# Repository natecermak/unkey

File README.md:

# Acoustic Underwater Text-based Communication Device (Name TBD)

## Purpose/Motivation
Divers often need to communicate with one another or with a dive boat, but typically can only communicate when in visual range of each other. A simple means to communicate with a bandwidth of text messaging (~40 wpm) over distances of several hundred meters could potentially save lives when if other divers or the dive boat can be made aware of and respond to unexpected conditions/situations.

## Communication scheme overview
Acoustic communication is basically the only feasible scheme underwater, and hence has been the standard for underwater communication since at least the early 1900s. Electromagnetic signals penetrate very poorly underwater, so convential means of communication (cellular communication, radio/walkie-talkies, bluetooth, wifi) are not feasible. Optical signaling is sometimes feasible (e.g. with flashlights), but relies on line of sight and good water clarity, and has limited range due to scattering and absorption underwater. However, if one has ever heard dolphins or whales underwater, they can attest to the immense distances these signals can travel, greatly exceeding the distance one can see underwater.

Underwater environments (a) add a lot of noise and (b) distort signals due to reflections.

Here, we use **binary frequency-shift keying (BFSK)** to send bits. See [Transmit / Receive Signal Flow](#transmit--receive-signal-flow) for how modulation and demodulation work.

## Subsystems:

### Keyboard
To get around difficulties with mechanical keys, we chose to use magnetic sensors and a magnet-bearing stylus. Underwater, mechanical keys have several failure modes:
 - They can break in such a way that allows water into the device, and
 - As one goes underwater, pressure increases, which eventually can press keys on its own, at which point buttons are stuck in the 'pressed' state, and basically useless.
We chose to use omnipolar Hall-effect switches, which have a digital output that changes from high to low when the magnetic flux through the device increases beyond some threshold. We rapidly read out every key's on/off state using an array of daisy-chained shift registers, an approach commonly used in other keyboards. When the user brings the magnet-tipped stylus near a sensor "key", the microcontroller can read the change in the Hall-effect switch output.

Users typically prefer some tactile feedback when they hit a key, and this system doesn't naturally provide that. As such, we experimented with adding a soft (low coercivity) magnetic material (1-2mm mild steel ball bearings) above the Hall-effect sensor, to provide a small pull-in magnetic force when the stylus is brought close to the key. This provides tacticle sensation to the user that they have actually touched a key. It's essential that this material is magnetizable so that it attracts the stylus, but also that it cannot develop a permanent magnetic moment. If it were to develop a permanent magnetic moment, it would turn the Hall-effect sensor on all the time and the key would be stuck "on".

Keyboard layout:
---------- Default, no modifier -------
1   2   3   4   5   6   7   8   9   0
q   w   e   r   t   y   u   i   o   p
  a   s   d   f   g   h   j   k   l   DEL
CAP z   x   c   v   b   n   m   ?   BCK
SYM      SPACESPACESPACESP   ,   .    RET
(plus 6 arrow keys, SEND)

---------- SYM modifier ---------------
!   @   #   $   %   ^   &   *   (   )
`   ~   -   _   =   +   :   ;   '   "
  [   ]   {   }   |   \   /   <   >   DEL
CAP z   x   c   v   b   n   m   ?   BCK
SYM      SPACESPACESPACESP   ,   .    RET

key count is:
    row 1: 10 keys
    row 2: 10 keys
    row 3: 10 keys
    row 4: 10 keys
    row 5: 5 keys
    off-grid: 6 arrow keys, 1 SEND key
Total: 52 keys

Non-character keys: 6 arrow keys, SEND, BCK, DEL, CAP, SYM

Future work could use open-drain hall-effect sensors in a grid to give more precise hit-boxes (e.g. a 2x2 grid of AH1925-HK4-7, wired in parallel, for each key). However, this would be significantly more expensive, as it would require roughly 4x as many switches.

### Microcontroller
We use a Teensy 4.1 microcontroller due to ease of development. Essential features this microcontroller provides are:
 - rapid (~100 ksps) ADC readout via DMA
 - SPI peripheral for driving a TFT LCD scree
n - DMA-compatible SPI peripheral for driving a DAC
 - I2C peripheral for controlling an external switch matrix
However, many other microcontrollers would likely work fine for this system.

### Battery
We use a rechargeable lithium ion battery, which provides a nominal 3.7V input.

### Transducer
We use a 45mm x 45mm x 1.4mm square piezo plate from Steminc (SMPL45W45T14111) as a transducer. This piezo is spec'd as having a capacitance of 5.4nF +- 20%. It's made from material SM111, which has a piezo d33 constant of 320e-12 C/N.

We made some measurements of the impedance at various frequencies:
    - Frequency   Real      Imaginary     (Capacitance, Q)
    -  0.1 kHz:   570    -  103.5k imag   (15.3nF, Q=182)
    -  1.0 kHz:    45    -   10.42k imag  (15.3nF, Q=236)
    - 10.0 kHz:     2.9  -    1.03k imag  (15.4nF, Q=356)
    - 40.0 kHz:     2.25 -       63 imag  (63.0nF, Q=28)
    -100.0 kHz:    -0.09 -      132 imag  (12nF,   Q=1350)

Overall, this seems pretty discrepant with their claim of 5.4nF. Given two parallel plates of this size, separated by 1.4mm, and a dielectric constant of 1400 (also from the [SM111 materials page](http://www.steminc.com/piezo/PZ_property.asp)), the calculated capacitance should be 17.9nF, closer to our measured value than their spec.

We also purchased several other transducers to try out, but have not yet used/characterized ther others:
- SMD25T14F15111 - Piezo Ceramic Disc 25x1.4mm R 1.5 Mhz          1.9 nF
- SMD50T21F1000R - Piezo Electric Disc 50x2.1mm R 1 MHz           10 nF

### Transducer driver

### Transducer sensor
We use a charge amplifier circuit with a configurable gain.

### Sensor data processing
We use Goertzel filters to extract amplitude and phase at a fixed set of frequencies.

### Screen
TBD.

### Enclosure
TBD.

## Version history:
v1.2 PCB changes:
 - [X] switch from teensy 4.1 to t4 for space
 - [X] add battery monitor circuitry
 - [X] replicate LiIon charger circuit on it https://github.com/adafruit/Adafruit-USB-LiIon-LiPoly-Charger-PCB/tree/master
 - [X] switch shift registers to qfn
 - [X] redo keyboard layout
 - [X] add 40-pin ZIF connector for 3.2" TFT from buydisplay.com
 - [X] make all passives 0402 for consistency
 - [X] add explicit space for screen
 - [X] add explicit space for battery
 - [X] add explicit space for Qi charger coil + PCB
 - [X] pull LAT down on MCP4, or just wire it out -- cant leave it floating
 - [X] CE on 5V boost wont work! needs to be always enabled, and drive a switch
 - [X] figure out FMARK and RD on ZIF connector for display: tested with them floating and display still works, so non-essential

v1.3 pcb
 - [X] split board into two separate parts with explicit design for overall assembly. This is for two reasons:
    1. so that I can do single-sided assembly on both pieces, but then have some parts sticking up (keyboard) and some facing down (teensy/driver electronics)
    2. it makes the face of the screen flush with the face of the magnetic switches.
 - [X] fix TFT connector pin numbering (it's backwards from the connector)
 - [X] make an attempt at a BOM

---
## Transmit / Receive Signal Flow

### Signal Modulation Process:

Unkey uses binary frequency-shift keying (BFSK) to transmit data acoustically. Each bit is encoded as a short sine wave at one of two fixed frequencies: one frequency represents a 0, and the other represents a 1. Bits are sent at a fixed bit rate, and bytes are transmitted MSB-first. Each packet begins with a known alternating preamble pattern, followed by framed payload bytes and an explicit footer. The preamble exists solely to help the receiver discover bit timing and alignment before attempting to decode data.

On the transmit side, text messages are packetized into bytes, converted into a bit stream, and then emitted as a sequence of tone windows via the DAC and piezo transducer. Each window contains a single tone corresponding to the current bit.

### Receiver Demodulation Process:

The receiver samples audio continuously using the ADC and DMA, processing fixed-size time windows of samples. For each window, it runs two Goertzel detectors—one tuned to each BFSK frequency—and measures their relative magnitudes. If neither tone is strong enough, the window is treated as noise and ignored.

Rather than assuming fixed timing, the receiver first builds a rolling history of recent window-level tone decisions. Once enough history is collected and the average signal strength is high enough, the receiver searches this history for the known alternating preamble pattern. It does this by trying both possible window alignments and checking for repeated tone flips; when a consistent pattern is found, bit boundaries are considered “locked.”

After timing is locked, each aligned window produces a real bit. These bits are accumulated and scanned for valid packet framing (header and footer). When a complete frame is detected, the payload is extracted, validated, and delivered to the chat system. If the signal weakens or framing fails for too long, the receiver drops alignment and returns to waiting for the preamble.

---

## Firmware File Organization

```
firmware/
├── platformio.ini
├── include/                  # All header files
│   ├── battery.h
│   ├── chat_logic.h
│   ├── comm.h
│   ├── config.h              # Shared constants, types, UI/chat/layout settings
│   ├── display.h
│   ├── goertzel.h
│   ├── hardware_config.h     # Pin assignments and hardware setup
│   └── keyboard.h
├── src/                      # Main firmware source code
│   ├── battery.cpp
│   ├── chat_logic.cpp        # Message buffer, scrolling, state management
│   ├── comm.cpp              # Encode/decode bits, tx/rx state
│   ├── display.cpp           # Drawing chat, keyboard, cursor
│   ├── goertzel.cpp          # Frequency detection (demodulation)
│   ├── keyboard.cpp          # Polling, key states, modifiers, stylus interaction
│   └── main.cpp              # Entry point: setup(), loop(), high-level orchestration
├── test/                     # Unit test suites (organized by feature and file)
│   ├── receiving/
│   │   ├── test_adc_buffer_full_interrupt/
│   │   │   └── adc_buffer_full_interrupt.cpp
│   │   ├── test_check_for_complete_packet/
│   │   │   └── check_for_complete_packet.cpp
│   │   ├── test_deliver_message/
│   │   │   └── deliver_message.cpp
│   │   ├── test_get_bit_from_top_frequency/
│   │   │   └── get_bit_from_top_frequency.cpp
│   │   ├── test_decode_single_bit_from_adc_window/
│   │   │   └── decode_single_bit_from_adc_window.cpp
│   ├── transmitting/
│   │   └── test_packetize_message/
│   │       └── packetize_message.cpp
│   ├── mock_display.cpp
│   └── mock_display.h
```

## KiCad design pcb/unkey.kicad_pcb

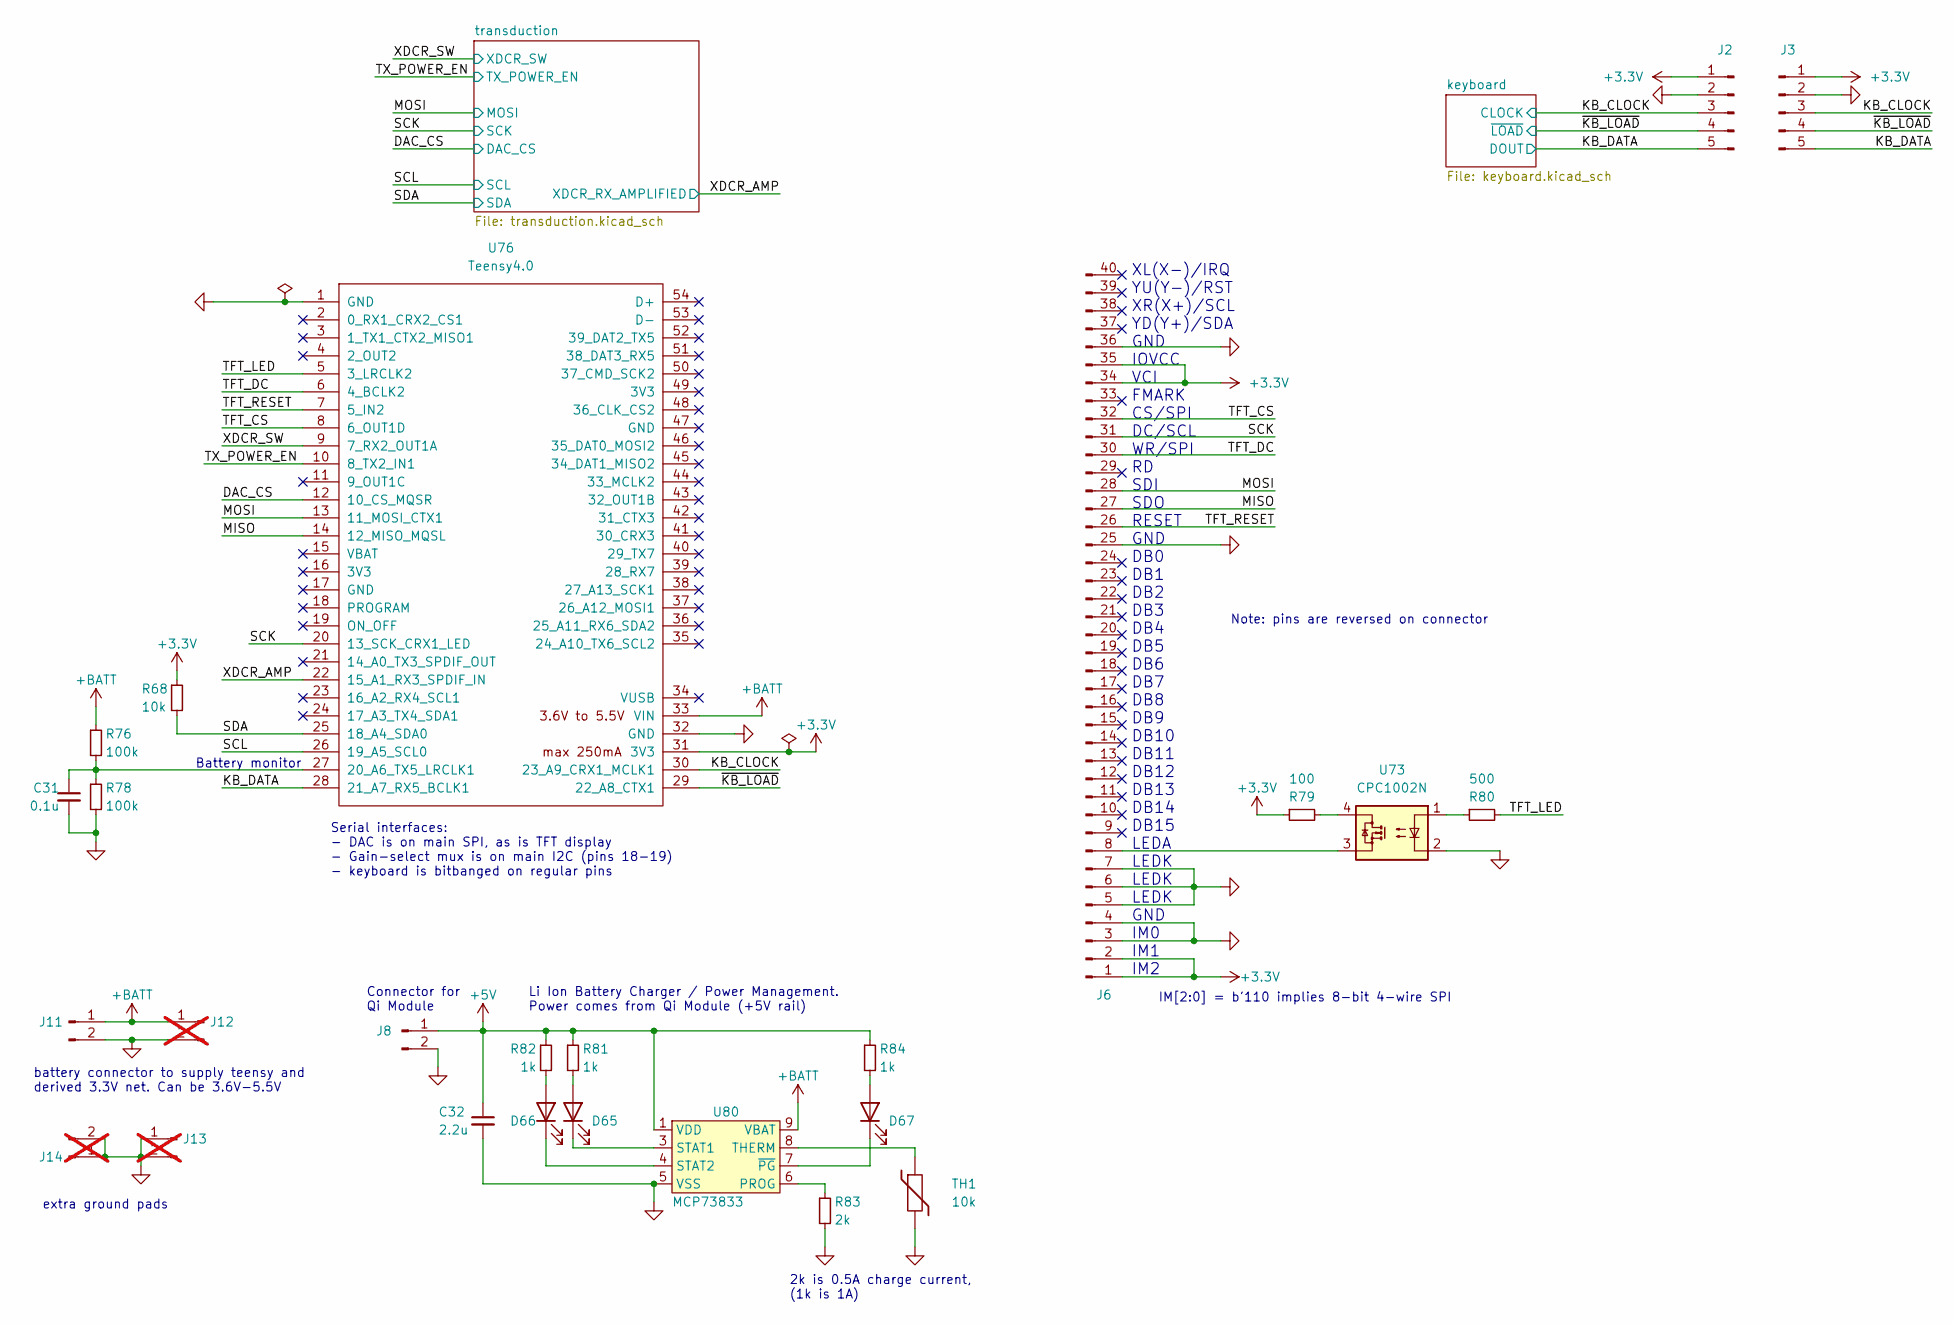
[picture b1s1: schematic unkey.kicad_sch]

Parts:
C31: 0.1u; C_0402_1005Metric; MPN CL05A104KA5NNNC; Digikey PN 1276-1043-1-ND
C32: 2.2u; C_0402_1005Metric; MPN C1005X5R1V225K050BC; Digikey PN 445-9028-1-ND
D65, D66, D67: LED; LED_0603_1608Metric; MPN 754-1116-1-ND; Digikey PN APT1608CGCK
J2, J3: Conn_01x05_Pin; PinHeader_1x05_P2.54mm_Vertical
J6: Conn_01x40_Pin; Hirose_FH12-40S-0.5SH_1x40-1MP_P0.50mm_Horizontal; MPN FH12A-40S-0.5SH(55); Digikey PN HFK140CT-ND
J8, J11: Conn_01x02_Pin; PinHeader_1x02_P2.54mm_Vertical
J12, J13, J14: Conn_01x02_Pin; PinHeader_1x02_P2.54mm_Vertical; not fitted
R68: 10k; R_0402_1005Metric
R76, R78: 100k; R_0402_1005Metric
R79: 100; R_0402_1005Metric
R80: 500; R_0402_1005Metric
R81, R82, R84: 1k; R_0402_1005Metric
R83: 2k; R_0402_1005Metric
TH1: 10k; R_0402_1005Metric; MPN NCU15XH103F6SRC; Digikey PN 490-NCU15XH103F6SRCCT-ND
U73: CPC1002N; SOP-4_3.8x4.1mm_P2.54mm; MPN CPC1002N; Digikey PN CLA221-ND
U76: Teensy4.0; Teensy40; MPN TEENSY 4.0 (HEADERS); Digikey PN DEV-16997
U80: MCP73833; DFN-10-1EP_3x3mm_P0.5mm_EP1.58x2.35mm; MPN MCP73833T-AMI/MF; Digikey PN MCP73833T-AMI/MFCT-ND

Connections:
+3.3V: J2.1, J3.1, J6.1, J6.2, J6.34, J6.35, R68.1, R79.1, U76.31 (3V3); also elsewhere on the board
+5V: C32.1, J8.1, R81.1, R82.1, R84.1, U80.1 (VDD), U80.2 (VDD)
+BATT: J11.1, J12.1, R76.1, U76.33 (VIN), U80.9 (VBAT), U80.10 (VBAT); also elsewhere on the board
/DAC_CS: U76.12 (10_CS_MQSR); also elsewhere on the board
/KB_CLOCK: J2.3, J3.3, U76.30 (23_A9_CRX1_MCLK1); also elsewhere on the board
/KB_DATA: J2.5, J3.5, U76.28 (21_A7_RX5_BCLK1); also elsewhere on the board
/MISO: J6.27, U76.14 (12_MISO_MQSL)
/MOSI: J6.28, U76.13 (11_MOSI_CTX1); also elsewhere on the board
/SCK: J6.31, U76.20 (13_SCK_CRX1_LED); also elsewhere on the board
/SCL: U76.26 (19_A5_SCL0); also elsewhere on the board
/SDA: R68.2, U76.25 (18_A4_SDA0); also elsewhere on the board
/TFT_CS: J6.32, U76.8 (6_OUT1D)
/TFT_DC: J6.30, U76.6 (4_BCLK2)
/TFT_LED: R80.2, U76.5 (3_LRCLK2)
/TFT_RESET: J6.26, U76.7 (5_IN2)
/TX_POWER_EN: U76.10 (8_TX2_IN1); also elsewhere on the board
/XDCR_AMP: U76.22 (15_A1_RX3_SPDIF_IN); also elsewhere on the board
/XDCR_SW: U76.9 (7_RX2_OUT1A); also elsewhere on the board
/~KB_LOAD: J2.4, J3.4, U76.29 (22_A8_CTX1); also elsewhere on the board
GND: C31.2, C32.2, J2.2, J3.2, J6.3, J6.4, J6.5, J6.6, J6.7, J6.25, J6.36, J8.2, J11.2, J12.2, J13.1, J13.2, J14.1, J14.2, R78.2, R83.2, TH1.2, U73.2, U76.1 (GND), U76.32 (GND), U80.5 (VSS), U80.11 (EP); also elsewhere on the board
unnamed: D65.2 (A), R81.2
unnamed: D65.1 (K), U80.3 (STAT1)
unnamed: D66.2 (A), R82.2
unnamed: D66.1 (K), U80.4 (STAT2)
unnamed: D67.2 (A), R84.2
unnamed: D67.1 (K), U80.7 (~PG)
unnamed: J6.8, U73.3
unnamed: R79.2, U73.4
unnamed: R80.1, U73.1
unnamed: C31.1, R76.2, R78.1, U76.27 (20_A6_TX5_LRCLK1)
unnamed: R83.1, U80.6 (PROG)
unnamed: TH1.1, U80.8 (THERM)

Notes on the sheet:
extra ground pads
2k is 0.5A charge current, (1k is 1A)
Note: pins are reversed on connector
XL(X-)/IRQ YU(Y-)/RST XR(X+)/SCL YD(Y+)/SDA GND IOVCC VCI FMARK CS/SPI DC/SCL WR/SPI RD SDI SDO RESET GND DB0 DB1 DB2 DB3 DB4 DB5 DB6 DB7 DB8 DB9 DB10 DB11 DB12 DB13 DB14 DB15 LEDA LEDK LEDK LEDK GND IM0 IM1 IM2
Li Ion Battery Charger / Power Management. Power comes from Qi Module (+5V rail)
IM[2:0] = b'110 implies 8-bit 4-wire SPI
Battery monitor
Connector for Qi Module
battery connector to supply teensy and derived 3.3V net. Can be 3.6V-5.5V
Serial interfaces: - DAC is on main SPI, as is TFT display - Gain-select mux is on main I2C (pins 18-19) - keyboard is bitbanged on regular pins

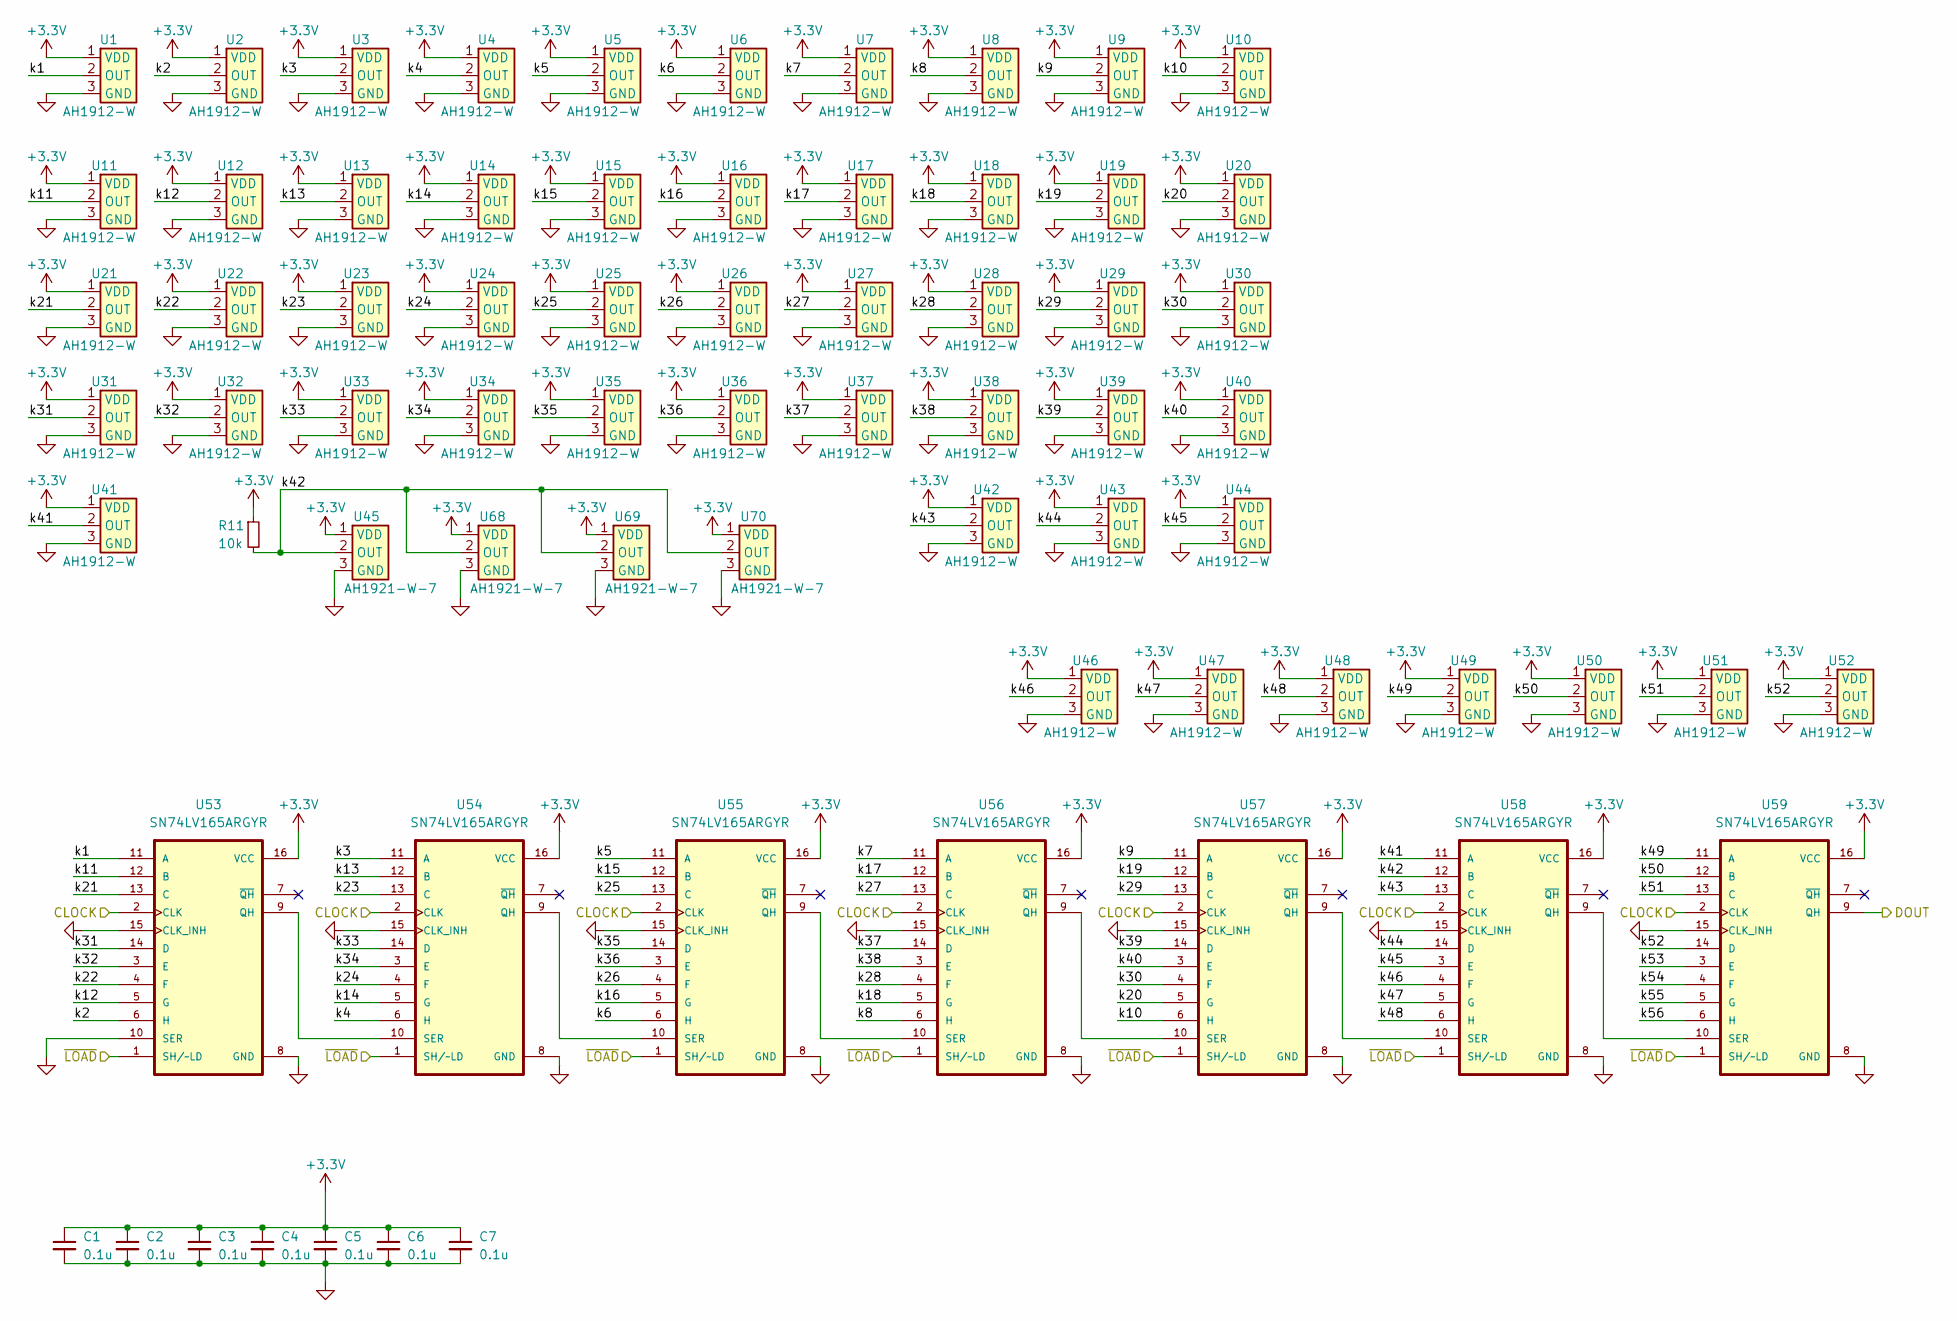
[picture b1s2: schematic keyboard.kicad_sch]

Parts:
C1, C2, C3, C4, C5, C6, C7: 0.1u; C_0402_1005Metric; MPN CL05A104KA5NNNC; Digikey PN 1276-1043-1-ND
R11: 10k; R_0402_1005Metric
U1, U2, U3, U4, U5, U6, U7, U8, U9, U10, U11, U12, U13, U14, U15, U16, U17, U18, U19, U20, U21, U22, U23, U24, U25, U26, U27, U28, U29, U30, U31, U32, U33, U34, U35, U36, U37, U38, U39, U40, U41, U42, U43, U44, U46, U47, U48, U49, U50, U51, U52: AH1912-W; SC-59; MPN AH1912-W-7; Digikey PN AH1912-W-7DICT-ND
U45, U68, U69, U70: AH1921-W-7; SC-59; MPN AH1921-W-7; Digikey PN AH1921-W-7DICT-ND
U53, U54, U55, U56, U57, U58, U59: SN74LV165ARGYR; Texas_RGY_R-PVQFN-N16_EP2.05x2.55mm; MPN SN74LV165ARGYR; Digikey PN 296-13937-1-ND

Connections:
+3.3V: C1.1, C2.1, C3.1, C4.1, C5.1, C6.1, C7.1, R11.1, U1.1 (VDD), U2.1 (VDD), U3.1 (VDD), U4.1 (VDD), U5.1 (VDD), U6.1 (VDD), U7.1 (VDD), U8.1 (VDD), U9.1 (VDD), U10.1 (VDD), U11.1 (VDD), U12.1 (VDD), U13.1 (VDD), U14.1 (VDD), U15.1 (VDD), U16.1 (VDD), U17.1 (VDD), U18.1 (VDD), U19.1 (VDD), U20.1 (VDD), U21.1 (VDD), U22.1 (VDD), U23.1 (VDD), U24.1 (VDD), U25.1 (VDD), U26.1 (VDD), U27.1 (VDD), U28.1 (VDD), U29.1 (VDD), U30.1 (VDD), U31.1 (VDD), U32.1 (VDD), U33.1 (VDD), U34.1 (VDD), U35.1 (VDD), U36.1 (VDD), U37.1 (VDD), U38.1 (VDD), U39.1 (VDD), U40.1 (VDD), U41.1 (VDD), U42.1 (VDD), U43.1 (VDD), U44.1 (VDD), U45.1 (VDD), U46.1 (VDD), U47.1 (VDD), U48.1 (VDD), U49.1 (VDD), U50.1 (VDD), U51.1 (VDD), U52.1 (VDD), U53.16 (VCC), U54.16 (VCC), U55.16 (VCC), U56.16 (VCC), U57.16 (VCC), U58.16 (VCC), U59.16 (VCC), U68.1 (VDD), U69.1 (VDD), U70.1 (VDD); also elsewhere on the board
/KB_CLOCK: U53.2 (CLK), U54.2 (CLK), U55.2 (CLK), U56.2 (CLK), U57.2 (CLK), U58.2 (CLK), U59.2 (CLK); also elsewhere on the board
/KB_DATA: U59.9 (QH); also elsewhere on the board
/keyboard/k1: U1.2 (OUT), U53.11 (A)
/keyboard/k2: U2.2 (OUT), U53.6 (H)
/keyboard/k3: U3.2 (OUT), U54.11 (A)
/keyboard/k4: U4.2 (OUT), U54.6 (H)
/keyboard/k5: U5.2 (OUT), U55.11 (A)
/keyboard/k6: U6.2 (OUT), U55.6 (H)
/keyboard/k7: U7.2 (OUT), U56.11 (A)
/keyboard/k8: U8.2 (OUT), U56.6 (H)
/keyboard/k9: U9.2 (OUT), U57.11 (A)
/keyboard/k10: U10.2 (OUT), U57.6 (H)
/keyboard/k11: U11.2 (OUT), U53.12 (B)
/keyboard/k12: U12.2 (OUT), U53.5 (G)
/keyboard/k13: U13.2 (OUT), U54.12 (B)
/keyboard/k14: U14.2 (OUT), U54.5 (G)
/keyboard/k15: U15.2 (OUT), U55.12 (B)
/keyboard/k16: U16.2 (OUT), U55.5 (G)
/keyboard/k17: U17.2 (OUT), U56.12 (B)
/keyboard/k18: U18.2 (OUT), U56.5 (G)
/keyboard/k19: U19.2 (OUT), U57.12 (B)
/keyboard/k20: U20.2 (OUT), U57.5 (G)
/keyboard/k21: U21.2 (OUT), U53.13 (C)
/keyboard/k22: U22.2 (OUT), U53.4 (F)
/keyboard/k23: U23.2 (OUT), U54.13 (C)
/keyboard/k24: U24.2 (OUT), U54.4 (F)
/keyboard/k25: U25.2 (OUT), U55.13 (C)
/keyboard/k26: U26.2 (OUT), U55.4 (F)
/keyboard/k27: U27.2 (OUT), U56.13 (C)
/keyboard/k28: U28.2 (OUT), U56.4 (F)
/keyboard/k29: U29.2 (OUT), U57.13 (C)
/keyboard/k30: U30.2 (OUT), U57.4 (F)
/keyboard/k31: U31.2 (OUT), U53.14 (D)
/keyboard/k32: U32.2 (OUT), U53.3 (E)
/keyboard/k33: U33.2 (OUT), U54.14 (D)
/keyboard/k34: U34.2 (OUT), U54.3 (E)
/keyboard/k35: U35.2 (OUT), U55.14 (D)
/keyboard/k36: U36.2 (OUT), U55.3 (E)
/keyboard/k37: U37.2 (OUT), U56.14 (D)
/keyboard/k38: U38.2 (OUT), U56.3 (E)
/keyboard/k39: U39.2 (OUT), U57.14 (D)
/keyboard/k40: U40.2 (OUT), U57.3 (E)
/keyboard/k41: U41.2 (OUT), U58.11 (A)
/keyboard/k42: R11.2, U45.2 (OUT), U58.12 (B), U68.2 (OUT), U69.2 (OUT), U70.2 (OUT)
/keyboard/k43: U42.2 (OUT), U58.13 (C)
/keyboard/k44: U43.2 (OUT), U58.14 (D)
/keyboard/k45: U44.2 (OUT), U58.3 (E)
/keyboard/k46: U46.2 (OUT), U58.4 (F)
/keyboard/k47: U47.2 (OUT), U58.5 (G)
/keyboard/k48: U48.2 (OUT), U58.6 (H)
/keyboard/k49: U49.2 (OUT), U59.11 (A)
/keyboard/k50: U50.2 (OUT), U59.12 (B)
/keyboard/k51: U51.2 (OUT), U59.13 (C)
/keyboard/k52: U52.2 (OUT), U59.14 (D)
/keyboard/k53: U59.3 (E)
/keyboard/k54: U59.4 (F)
/keyboard/k55: U59.5 (G)
/keyboard/k56: U59.6 (H)
/~KB_LOAD: U53.1 (SH/~LD), U54.1 (SH/~LD), U55.1 (SH/~LD), U56.1 (SH/~LD), U57.1 (SH/~LD), U58.1 (SH/~LD), U59.1 (SH/~LD); also elsewhere on the board
GND: C1.2, C2.2, C3.2, C4.2, C5.2, C6.2, C7.2, U1.3 (GND), U2.3 (GND), U3.3 (GND), U4.3 (GND), U5.3 (GND), U6.3 (GND), U7.3 (GND), U8.3 (GND), U9.3 (GND), U10.3 (GND), U11.3 (GND), U12.3 (GND), U13.3 (GND), U14.3 (GND), U15.3 (GND), U16.3 (GND), U17.3 (GND), U18.3 (GND), U19.3 (GND), U20.3 (GND), U21.3 (GND), U22.3 (GND), U23.3 (GND), U24.3 (GND), U25.3 (GND), U26.3 (GND), U27.3 (GND), U28.3 (GND), U29.3 (GND), U30.3 (GND), U31.3 (GND), U32.3 (GND), U33.3 (GND), U34.3 (GND), U35.3 (GND), U36.3 (GND), U37.3 (GND), U38.3 (GND), U39.3 (GND), U40.3 (GND), U41.3 (GND), U42.3 (GND), U43.3 (GND), U44.3 (GND), U45.3 (GND), U46.3 (GND), U47.3 (GND), U48.3 (GND), U49.3 (GND), U50.3 (GND), U51.3 (GND), U52.3 (GND), U53.8 (GND), U53.10 (SER), U53.15 (CLK_INH), U54.8 (GND), U54.15 (CLK_INH), U55.8 (GND), U55.15 (CLK_INH), U56.8 (GND), U56.15 (CLK_INH), U57.8 (GND), U57.15 (CLK_INH), U58.8 (GND), U58.15 (CLK_INH), U59.8 (GND), U59.15 (CLK_INH), U68.3 (GND), U69.3 (GND), U70.3 (GND); also elsewhere on the board
unnamed: U53.9 (QH), U54.10 (SER)
unnamed: U54.9 (QH), U55.10 (SER)
unnamed: U55.9 (QH), U56.10 (SER)
unnamed: U56.9 (QH), U57.10 (SER)
unnamed: U57.9 (QH), U58.10 (SER)
unnamed: U58.9 (QH), U59.10 (SER)

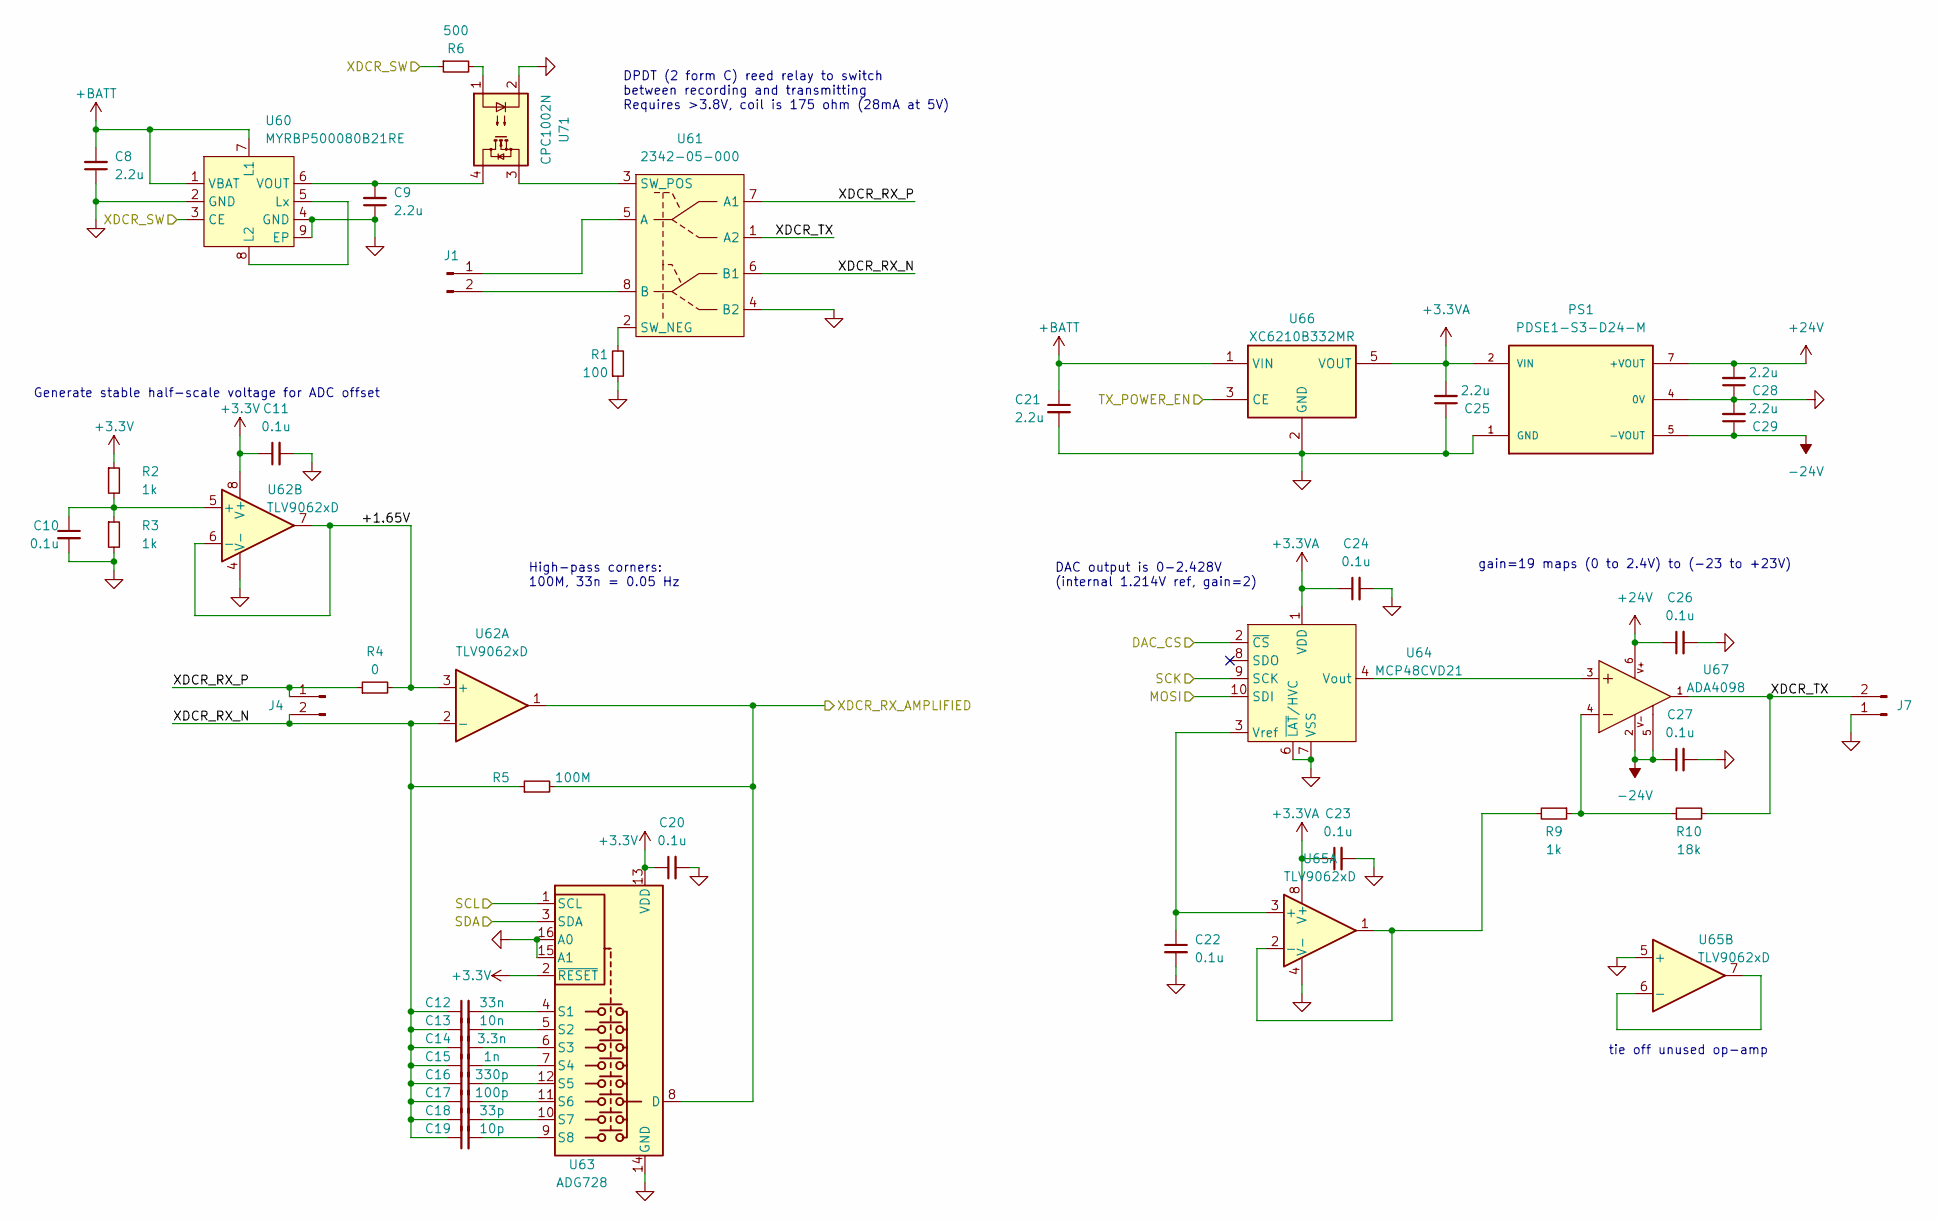
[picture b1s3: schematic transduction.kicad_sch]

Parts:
C8, C9, C21, C25, C28, C29: 2.2u; C_0402_1005Metric; MPN C1005X5R1V225K050BC; Digikey PN 445-9028-1-ND
C10, C11, C20, C22, C23, C24, C26, C27: 0.1u; C_0402_1005Metric; MPN CL05A104KA5NNNC; Digikey PN 1276-1043-1-ND
C12: 33n; C_0402_1005Metric
C13: 10n; C_0402_1005Metric
C14: 3.3n; C_0402_1005Metric
C15: 1n; C_0402_1005Metric
C16: 330p; C_0402_1005Metric
C17: 100p; C_0402_1005Metric
C18: 33p; C_0402_1005Metric
C19: 10p; C_0402_1005Metric
J1, J4, J7: Conn_01x02_Pin; PinHeader_1x02_P2.54mm_Vertical
PS1: PDSE1-S3-D24-M; CONV_PDSE1-S3-D24-M; PARTREV 1.0; Digikey PN 102-PDSE1-S3-D24-M-ND
R1: 100; R_0402_1005Metric
R2, R3, R9: 1k; R_0402_1005Metric
R4: 0; R_0402_1005Metric
R5: 100M; R_0402_1005Metric; MPN HMC0402JT100M; Digikey PN HMC0402JT100MCT-ND
R6: 500; R_0402_1005Metric
R10: 18k; R_0402_1005Metric
U60: MYRBP500080B21RE; MPN MYRBP500080B21RE; Digikey PN 811-MYRBP500080B21RECT-ND
U61: 2342-05-000; MPN 2342-05-000; Digikey PN 306-1111-ND
U62: TLV9062xD; SOIC-8_3.9x4.9mm_P1.27mm; MPN TLV9062IDR; Digikey PN 296-47857-1-ND
U63: ADG728; TSSOP-16_4.4x5mm_P0.65mm; MPN ADG728BRUZ-REEL7; Digikey PN 505-ADG728BRUZ-REEL7CT-ND
U64: MCP48CVD21; DFN-10-1EP_3x3mm_P0.5mm_EP1.55x2.48mm; MPN MCP48CVD21T-E/MF; Digikey PN 150-MCP48CVD21T-E/MFCT-ND
U65: TLV9062xD; SOIC-8_3.9x4.9mm_P1.27mm
U66: XC6210B332MR; SOT-23-5; MPN XC6210B332MR-G; Digikey PN 893-1075-1-ND
U67: ADA4098; SOT-23-6; PARTREV A; Digikey PN 505-ADA4098-1BUJZ-RL7CT-ND
U71: CPC1002N; SOP-4_3.8x4.1mm_P2.54mm; MPN CPC1002N; Digikey PN CLA221-ND

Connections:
+3.3V: C11.1, C20.1, R2.1, U62.8 (V+), U63.2 (~RESET), U63.13 (VDD); also elsewhere on the board
+3.3VA: C23.1, C24.1, C25.2, PS1.2 (VIN), U64.1 (VDD), U65.8 (V+), U66.5 (VOUT)
+24V: C26.1, C28.2, PS1.7 (+VOUT), U67.6
+BATT: C8.2, C21.1, U60.1 (VBAT), U60.7 (L1), U66.1 (VIN); also elsewhere on the board
-24V: C27.1, C29.1, PS1.5 (-VOUT), U67.2, U67.5
/DAC_CS: U64.2 (~CS); also elsewhere on the board
/MOSI: U64.10 (SDI); also elsewhere on the board
/SCK: U64.9 (SCK); also elsewhere on the board
/SCL: U63.1 (SCL); also elsewhere on the board
/SDA: U63.3 (SDA); also elsewhere on the board
/TX_POWER_EN: U66.3 (CE); also elsewhere on the board
/XDCR_AMP: R5.2, U62.1, U63.8 (D); also elsewhere on the board
/XDCR_SW: R6.1, U60.3 (CE); also elsewhere on the board
/transduction/+1.65V: R4.2, U62.3 (+), U62.6 (-), U62.7
/transduction/XDCR_RX_N: C12.1, C13.1, C14.1, C15.1, C16.1, C17.1, C18.1, C19.1, J4.2, R5.1, U61.6 (B1), U62.2 (-)
/transduction/XDCR_RX_P: J4.1, R4.1, U61.7 (A1)
/transduction/XDCR_TX: J7.2, R10.2, U61.1 (A2), U67.1
GND: C8.1, C9.1, C10.2, C11.2, C20.2, C21.2, C22.2, C23.2, C24.2, C25.1, C26.2, C27.2, C28.1, C29.2, J7.1, PS1.1 (GND), PS1.4 (0V), R1.1, R3.2, U60.2 (GND), U60.4 (GND), U60.9 (EP), U61.4 (B2), U62.4 (V-), U63.14 (GND), U63.15 (A1), U63.16 (A0), U64.6 (~LAT/HVC), U64.7 (VSS), U65.4 (V-), U65.5 (+), U66.2 (GND), U71.2; also elsewhere on the board
unnamed: J1.1, U61.5 (A)
unnamed: J1.2, U61.8 (B)
unnamed: R6.2, U71.1
unnamed: R9.1, R10.1, U67.4
unnamed: U60.5 (Lx), U60.8 (L2)
unnamed: C9.2, U60.6 (VOUT), U71.4
unnamed: R1.2, U61.2 (SW_NEG)
unnamed: U61.3 (SW_POS), U71.3
unnamed: C10.1, R2.2, R3.1, U62.5 (+)
unnamed: C12.2, U63.4 (S1)
unnamed: C13.2, U63.5 (S2)
unnamed: C14.2, U63.6 (S3)
unnamed: C15.2, U63.7 (S4)
unnamed: C16.2, U63.12 (S5)
unnamed: C17.2, U63.11 (S6)
unnamed: C18.2, U63.10 (S7)
unnamed: C19.2, U63.9 (S8)
unnamed: U64.4 (Vout), U67.3
unnamed: C22.1, U64.3 (Vref), U65.3 (+)
unnamed: R9.2, U65.1, U65.2 (-)
unnamed: U65.6 (-), U65.7

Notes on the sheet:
gain=19 maps (0 to 2.4V) to (-23 to +23V)
Generate stable half-scale voltage for ADC offset
High-pass corners: 100M, 33n = 0.05 Hz
tie off unused op-amp
DPDT (2 form C) reed relay to switch between recording and transmitting Requires >3.8V, coil is 175 ohm (28mA at 5V)
DAC output is 0-2.428V (internal 1.214V ref, gain=2)

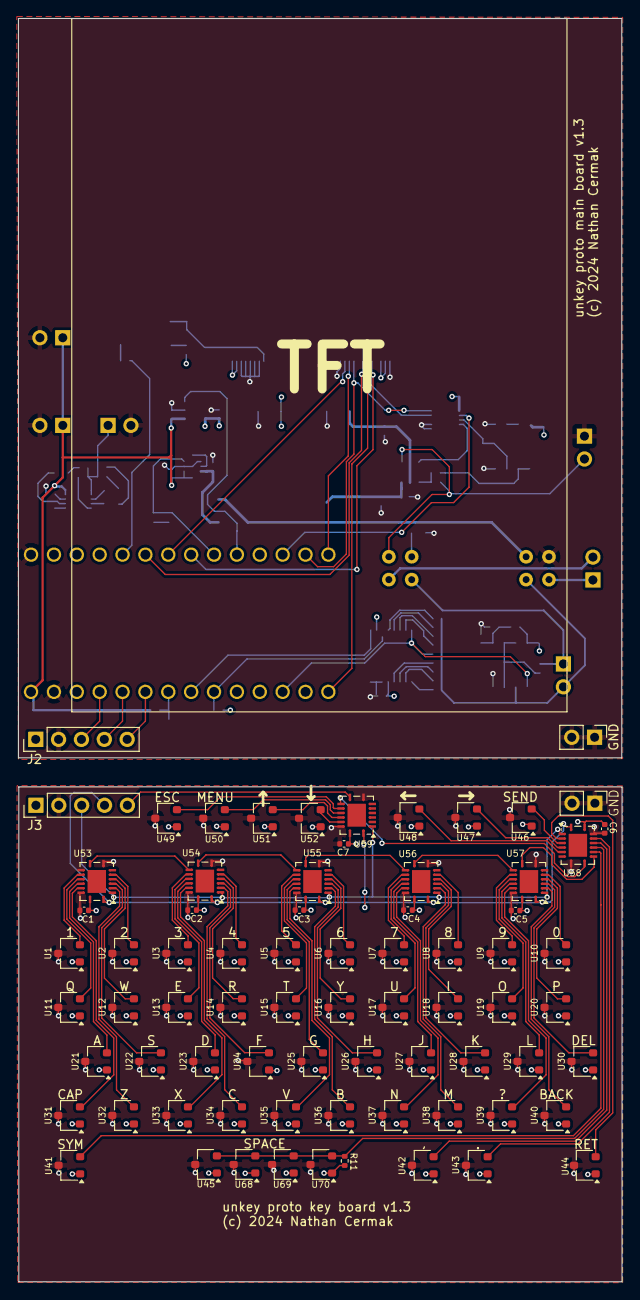
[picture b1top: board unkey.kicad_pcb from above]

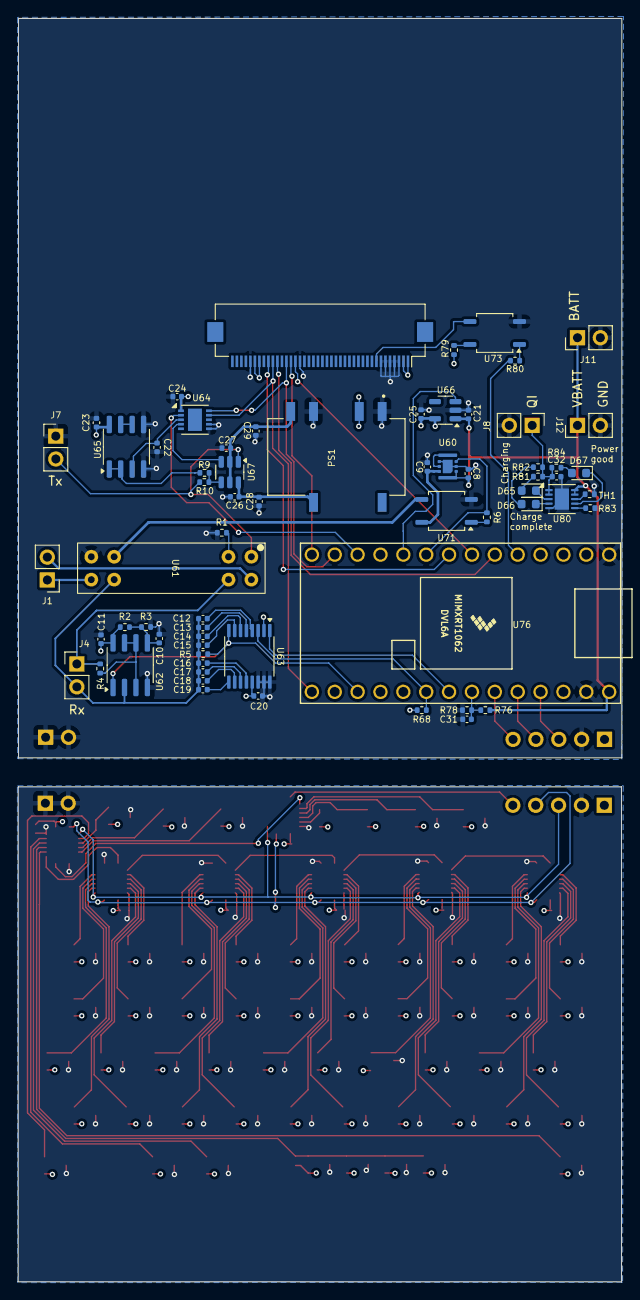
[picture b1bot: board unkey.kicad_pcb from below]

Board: 4 copper layers, 67.0 x 140.3 mm, 139 parts (65 on the bottom side), 118 nets.

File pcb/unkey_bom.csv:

"#","Reference","Qty","Value","Footprint","DNP","Digikey PN","URL"
"1","C1, C2, C3, C4, C5, C6, C7, C10, C11, C20, C22, C23, C24, C26, C27, C31","16","0.1u","Capacitor_SMD:C_0402_1005Metric","","1276-1043-1-ND","https://www.digikey.com/en/products/detail/samsung-electro-m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"
"2","C8, C9, C21, C25, C28, C29, C32","7","2.2u","Capacitor_SMD:C_0402_1005Metric","","445-9028-1-ND","https://www.digikey.com/en/products/detail/tdk-corporation/C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"
"3","C12","1","33n","Capacitor_SMD:C_0402_1005Metric","","",""
"4","C13","1","10n","Capacitor_SMD:C_0402_1005Metric","","",""
"5","C14","1","3.3n","Capacitor_SMD:C_0402_1005Metric","","",""
"6","C15","1","1n","Capacitor_SMD:C_0402_1005Metric","","",""
"7","C16","1","330p","Capacitor_SMD:C_0402_1005Metric","","",""
"8","C17","1","100p","Capacitor_SMD:C_0402_1005Metric","","",""
"9","C18","1","33p","Capacitor_SMD:C_0402_1005Metric","","",""
"10","C19","1","10p","Capacitor_SMD:C_0402_1005Metric","","",""
"11","D65, D66, D67","3","LED","LED_SMD:LED_0603_1608Metric","","APT1608CGCK","https://www.digikey.com/en/products/detail/kingbright/APT160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"
"12","J1, J4, J7, J8, J11","5","Conn_01x02_Pin","Connector_PinHeader_2.54mm:PinHeader_1x02_P2.54mm_Vertical","","",""
"13","J2, J3","2","Conn_01x05_Pin","Connector_PinHeader_2.54mm:PinHeader_1x05_P2.54mm_Vertical","","",""
"14","J6","1","Conn_01x40_Pin","Connector_FFC-FPC:Hirose_FH12-40S-0.5SH_1x40-1MP_P0.50mm_Horizontal","","https://www.digikey.com/en/products/detail/hirose-electric-c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","https://www.digikey.com/en/products/detail/hirose-electric-c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"
"15","J12, J13, J14","3","Conn_01x02_Pin","Connector_PinHeader_2.54mm:PinHeader_1x02_P2.54mm_Vertical","DNP","",""
"16","PS1","1","PDSE1-S3-D24-M","unkey-footprints:CONV_PDSE1-S3-D24-M","","102-PDSE1-S3-D24-M-ND","https://www.digikey.com/en/products/detail/cui-inc/PDSE1-S3-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"
"17","R1, R79","2","100","Resistor_SMD:R_0402_1005Metric","","",""
"18","R2, R3, R9, R81, R82, R84","6","1k","Resistor_SMD:R_0402_1005Metric","","",""
"19","R4","1","0","Resistor_SMD:R_0402_1005Metric","","",""
"20","R5","1","100M","Resistor_SMD:R_0402_1005Metric","","HMC0402JT100MCT-ND","https://www.digikey.com/en/products/detail/stackpole-electro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"
"21","R6, R80","2","500","Resistor_SMD:R_0402_1005Metric","","",""
"22","R10","1","18k","Resistor_SMD:R_0402_1005Metric","","",""
"23","R11, R68","2","10k","Resistor_SMD:R_0402_1005Metric","","",""
"24","R76, R78","2","100k","Resistor_SMD:R_0402_1005Metric","","",""
"25","R83","1","2k","Resistor_SMD:R_0402_1005Metric","","",""
"26","TH1","1","10k","Resistor_SMD:R_0402_1005Metric","","490-NCU15XH103F6SRCCT-ND","https://www.digikey.com/en/products/detail/murata-electronic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"
"27","U1, U2, U3, U4, U5, U6, U7, U8, U9, U10, U11, U12, U13, U14, U15, U16, U17, U18, U19, U20, U21, U22, U23, U24, U25, U26, U27, U28, U29, U30, U31, U32, U33, U34, U35, U36, U37, U38, U39, U40, U41, U42, U43, U44, U46, U47, U48, U49, U50, U51, U52","51","AH1912-W","Package_TO_SOT_SMD:SC-59","","AH1912-W-7DICT-ND","https://www.digikey.com/en/products/detail/diodes-incorporat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"
"28","U45, U68, U69, U70","4","AH1921-W-7","Package_TO_SOT_SMD:SC-59","","AH1921-W-7DICT-ND","https://www.digikey.com/en/products/detail/diodes-incorporat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"
"29","U53, U54, U55, U56, U57, U58, U59","7","SN74LV165ARGYR","Package_DFN_QFN:Texas_RGY_R-PVQFN-N16_EP2.05x2.55mm","","296-13937-1-ND","https://www.digikey.com/en/products/detail/texas-instruments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"
"30","U60","1","MYRBP500080B21RE","unkey-footprints:MYRBP500080B21RE","","811-MYRBP500080B21RECT-ND","https://www.digikey.com/en/products/detail/murata-power-solu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"
"31","U61","1","2342-05-000","unkey-footprints:2342-05-000","","306-1111-ND","https://www.digikey.com/en/products/detail/coto-technology/2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"
"32","U62, U65","2","TLV9062xD","Package_SO:SOIC-8_3.9x4.9mm_P1.27mm","","296-47857-1-ND","https://www.digikey.com/en/products/detail/texas-instruments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"
"33","U63","1","ADG728","Package_SO:TSSOP-16_4.4x5mm_P0.65mm","","505-ADG728BRUZ-REEL7CT-ND","https://www.digikey.com/en/products/detail/analog-devices-in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"
"34","U64","1","MCP48CVD21","Package_DFN_QFN:DFN-10-1EP_3x3mm_P0.5mm_EP1.55x2.48mm","","150-MCP48CVD21T-E/MFCT-ND","https://www.digikey.com/en/products/detail/microchip-technol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"
"35","U66","1","XC6210B332MR","Package_TO_SOT_SMD:SOT-23-5","","893-1075-1-ND","https://www.digikey.com/en/products/detail/torex-semiconduct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"
"36","U67","1","ADA4098","Package_TO_SOT_SMD:SOT-23-6","","505-ADA4098-1BUJZ-RL7CT-ND","https://www.digikey.com/en/products/detail/analog-devices-in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"
"37","U71, U73","2","CPC1002N","Package_SO:SOP-4_3.8x4.1mm_P2.54mm","","CLA221-ND","https://www.digikey.com/en/products/detail/ixys-integrated-c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"
"38","U76","1","Teensy4.0","unkey-footprints:Teensy40","","DEV-16997","https://www.digikey.com/en/products/detail/sparkfun-electron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"
"39","U80","1","MCP73833","Package_DFN_QFN:DFN-10-1EP_3x3mm_P0.5mm_EP1.58x2.35mm","","MCP73833T-AMI/MFCT-ND","https://www.digikey.com/en/products/detail/microchip-technol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"

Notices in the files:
pcb/unkey.kicad_pcb:
(c) 2024 Nathan Cermak
